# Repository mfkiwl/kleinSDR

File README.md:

# kleinSDR
Small SDR based on STM32.

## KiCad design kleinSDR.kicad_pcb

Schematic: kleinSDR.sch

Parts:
C1, C2, C3, C4, C5, C6, C7, C8, C9, C10, C11, C12, C13, C14, C15, C16, C17, C24, C25, C26, C28, C30, C33, C34, C35, C36, C37, C38, C39, C40, C41, C42, C43, C44, C46, C47, C48, C55, C58, C59, C61, C66, C72: 100nF; C_0603
C18, C19, C20, C21, C22, C23, C60, C62, C73, C74, C75, C76: 1nF; C_0603
C27, C29, C45: 4.7uF; C_0603
C31, C32: 2.2uF; C_0603
C49, C52, C63, C70: 10uF; C_0603
C50, C51: 470nF; C_0603
C53, C54, C67, C68, C69: 1uF; C_0603
C56, C57, C71: 220pF; C_0603
C64, C65: 220uF
J1: USB_B_Mini; USB_Mini-B_Lumberg_2486_01_Horizontal
J2: Frequency Dial; Pin_Header_Straight_1x04_Pitch2.54mm
J3: Boot0
J4: SWDP; Pin_Header_Straight_1x04_Pitch2.54mm
J5: UART
J6, J7: Line Out
J8: LINE IN
J9: MIC IN
J10: 30pin Board to Board
L1, L2: 47uH
Q1: BC857; SOT-23
R1, R2: 22E; R_0603
R3, R5: 10K; R_0603
R4, R11, R12, R22, R23, R32, R33: 47E; R_0603
R6, R7, R8, R9, R10, R15, R16, R17, R18, R21, R31: 100E; R_0603
R13, R14, R24, R25: 1K; R_0603
R19, R26, R27, R29, R30: 4k7; R_0603
R20: 680E; R_0603
R28: 47K; R_0603
SW1: PG6; SW_PUSH_6mm_h4.3mm
SW2: PB8; SW_PUSH_6mm_h4.3mm
SW3: PE4; SW_PUSH_6mm_h4.3mm
SW4: PG11; SW_PUSH_6mm_h4.3mm
SW5: PF0; SW_PUSH_6mm_h4.3mm
SW6: PB3; SW_PUSH_6mm_h4.3mm
SW7: PC1; SW_PUSH_6mm_h4.3mm
SW8: PA15; SW_PUSH_6mm_h4.3mm
SW9: PE2; SW_PUSH_6mm_h4.3mm
SW10: PG15; SW_PUSH_6mm_h4.3mm
SW11: PE3; SW_PUSH_6mm_h4.3mm
SW12: PE5; SW_PUSH_6mm_h4.3mm
SW13: PB0; SW_PUSH_6mm_h4.3mm
SW14: PB2; SW_PUSH_6mm_h4.3mm
SW15: PC4; SW_PUSH_6mm_h4.3mm
SW16: PC5; SW_PUSH_6mm_h4.3mm
SW17: PG2; SW_PUSH_6mm_h4.3mm
SW18: Volume; RotaryEncoder_Alps_EC12E_Vertical_H20mm
SW19: RF Gain; RotaryEncoder_Alps_EC12E_Vertical_H20mm
SW20: RIT; RotaryEncoder_Alps_EC12E_Vertical_H20mm
U1: FOX924B-16.000
U2: USBLC6-2SC6; SOT-23-6
U3: STM32F767ZITx; LQFP-144_20x20mm_Pitch0.5mm
U4, U6: WM8731; SSOP-28_5.3x10.2mm_Pitch0.65mm
U5: HY28B

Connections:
+3.3VA: C25.2, C27.2, R4.2, U3.33
+3.3VADC: C28.2, C29.2, R4.1, U3.32
+3V3: C30.2, C33.2, C34.2, C35.2, C36.2, C37.2, C38.2, C39.2, C40.2, C41.2, C42.2, C43.2, C44.2, C45.2, C47.2, C48.2, C49.2, C59.2, C61.2, C63.2, R5.2, R13.2, R14.2, R24.2, R25.2, U3.6, U3.17, U3.30, U3.39, U3.52, U3.62, U3.72, U3.84, U3.95, U3.108, U3.121, U3.131, U3.144, U4.1, U4.27, U6.1, U6.27
+5V: C24.2, J2.1
/ADC1: U3.42
/ADC2: U3.37
/ADC3: U3.13
/AUDIO_IN_I: C53.2, C56.2
/AUDIO_IN_Q: C54.2, C57.2
/AUDIO_OUT_I: C50.1
/AUDIO_OUT_Q: C51.1
/BAND0: U3.56
/BAND1: U3.100
/BAND2: U3.102
/ButtonBndM: C11.1, SW13.2, U3.46
/ButtonBndP: C12.1, SW14.2, U3.48
/ButtonF1: C8.1, SW8.2, U3.110
/ButtonF2: C9.1, SW9.2, U3.1
/ButtonF3: C10.1, SW10.2, U3.132
/ButtonF4: C14.1, SW11.2, U3.2
/ButtonF5: C15.1, SW12.2, U3.4
/ButtonG1: C1.1, SW1.2, U3.91
/ButtonG2: C2.1, SW2.2, U3.139
/ButtonG3: C6.1, SW3.2, U3.3
/ButtonG4: C7.1, SW4.2, U3.126
/ButtonM1: C3.1, SW5.2, U3.10
/ButtonM2: C4.1, SW6.2, U3.133
/ButtonM3: C5.1, SW7.2, U3.27
/ButtonPwr: C17.1, SW17.2, U3.87
/ButtonStpM: C13.1, SW15.2, U3.44
/ButtonStpP: C16.1, SW16.2, U3.45
/DAC1: U3.41
/EncFreq1: J2.2, U3.96
/EncFreq2: J2.3, U3.97
/EncRF1: C22.2, SW19.B, U3.81
/EncRF2: C19.2, SW19.A, U3.82
/EncRIT1: C23.2, SW20.B, U3.34
/EncRIT2: C20.2, SW20.A, U3.35
/EncVol1: C21.2, SW18.B, U3.134
/EncVol2: C18.2, SW18.A, U3.135
/I2C1_SCL: R32.2, U3.136
/I2C1_SDA: R33.2, U3.137
/I2C2_SCL: R22.1, R24.1, U3.69
/I2C2_SDA: R23.1, R25.1, U3.70
/I2C4_SCL: R11.1, R13.1, U3.54
/I2C4_SDA: R12.1, R14.1, U3.55
/LCD_BL: U3.116, U5.40
/LCD_CS: U3.123, U5.11
/LCD_D0: U3.85, U5.23
/LCD_D1: U3.86, U5.24
/LCD_D2: U3.114, U5.25
/LCD_D3: U3.115, U5.26
/LCD_D4: U3.58, U5.27
/LCD_D5: U3.59, U5.28
/LCD_D6: U3.60, U5.29
/LCD_D7: U3.63, U5.30
/LCD_D10: U3.64, U5.3
/LCD_D11: U3.65, U5.4
/LCD_D12: U3.66, U5.5
/LCD_D13: U3.67, U5.6
/LCD_D14: U3.68, U5.7
/LCD_D15: U3.77, U5.8
/LCD_D16: U3.78, U5.9
/LCD_D17: U3.79, U5.10
/LCD_RD: U3.118, U5.14
/LCD_RESET: U3.117, U5.15
/LCD_RS: U3.88, U5.12
/LCD_SDI: U5.17
/LCD_SDO: U5.16
/LCD_WR: U3.119, U5.13
/MICBIAS: R19.2, U3.93
/NRST: J4.1, U3.25
/PTT: C75.2, R31.2
/PTT_ON: U3.47
/PWR_DWN: U3.98
/SAI1_FS_B: R17.2, U3.21
/SAI1_MCLK_B: R21.1, U3.19
/SAI1_SCK_B: R15.2, U3.20
/SAI1_SD_A: R18.2, U3.122
/SAI1_SD_B: R16.2, U3.18
/SAI2_FS_B: R8.2, U3.26
/SAI2_MCLK_B: R10.1, U3.5
/SAI2_SCK_B: R6.2, U3.36
/SAI2_SD_A: R9.2, U3.80
/SAI2_SD_B: R7.2, U3.125
/SWCLK: J4.2, U3.109
/SWDIO: J4.3, U3.105
/TP_CS: U3.101, U5.32
/TP_IRQ: U3.89, U5.36
/TP_SCK: U3.74, U5.33
/TP_SDI: U3.29, U5.34
/TP_SDO: U3.28, U5.35
/UI_5V: U5.1
/USB_N: R1.1
/USB_OTG_FS_DM: R1.2, U3.103
/USB_OTG_FS_DP: R2.2, U3.104
/USB_P: R2.1
/xUSB_N: J1.2 (D-)
/xUSB_P: J1.3 (D+)
GND: C1.2, C2.2, C3.2, C4.2, C5.2, C6.2, C7.2, C8.2, C9.2, C10.2, C11.2, C12.2, C13.2, C14.2, C15.2, C16.2, C17.2, C18.1, C19.1, C20.1, C21.1, C22.1, C23.1, C24.1, C25.1, C26.1, C27.1, C28.1, C29.1, C30.1, C31.2, C32.2, C33.1, C34.1, C35.1, C36.1, C37.1, C38.1, C39.1, C40.1, C41.1, C42.1, C43.1, C44.1, C45.1, C46.1, C47.1, C48.1, C49.1, C52.1, C55.1, C56.1, C57.1, C58.1, C59.1, C60.1, C61.1, C62.1, C63.1, C66.1, C70.1, C71.1, C72.1, C73.1, C74.1, C75.1, C76.1, J1.5 (GND), J1.6 (Shield), J2.4, J4.4, R3.2, R26.2, R27.2, R28.1, SW1.1, SW2.1, SW3.1, SW4.1, SW5.1, SW6.1, SW7.1, SW8.1, SW9.1, SW10.1, SW11.1, SW12.1, SW13.1, SW14.1, SW15.1, SW16.1, SW17.1, SW18.C, SW19.C, SW20.C, U1.2, U3.16, U3.31, U3.38, U3.51, U3.61, U3.83, U3.94, U3.107, U3.120, U3.130, U4.11, U4.15, U4.21, U4.22, U4.28, U5.2, U5.19, U5.22, U5.39, U6.11, U6.15, U6.21, U6.22, U6.28
unnamed: C26.2, U1.4
unnamed: C31.1, U3.71
unnamed: C32.1, U3.106
unnamed: C50.2, U4.12
unnamed: C51.2, U4.13
unnamed: C52.2, C55.2, U4.16
unnamed: C53.1, U4.20
unnamed: C54.1, U4.19
unnamed: C66.2, R19.1
unnamed: C67.1, U6.20
unnamed: C67.2, R26.1, R29.1
unnamed: C68.1, U6.19
unnamed: C68.2, R27.1, R30.1
unnamed: C69.1, U6.18
unnamed: C69.2, C71.2, C73.2, R20.1, R28.2
unnamed: C70.2, C72.2, U6.16
unnamed: C74.2, R29.2
unnamed: C76.2, R30.2
unnamed: R3.1, U3.138
unnamed: R5.1, U3.143
unnamed: R6.1, U4.3
unnamed: R7.1, U4.4
unnamed: R8.1, U4.5, U4.7
unnamed: R9.1, U4.6
unnamed: R10.2, U4.25
unnamed: R11.2, U4.24
unnamed: R12.2, U4.23
unnamed: R15.1, U6.3
unnamed: R16.1, U6.4
unnamed: R17.1, U6.5, U6.7
unnamed: R18.1, U6.6
unnamed: R21.2, U6.25
unnamed: R22.2, U6.24
unnamed: R23.2, U6.23
unnamed: U1.3, U3.23
VBUS: J1.1 (VBUS)
VDDA: C46.2, C58.2, U4.8, U4.14, U6.8, U6.14

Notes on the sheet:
USB Connector
Buttons
Rotary Encoders
Frequency Dial Optical Encoder
SWDP & Debug Connectors
Vdd, Vbat Decoupling
Ceramic Low ESR
Vdda, Vref Decoupling
TO DO: 1. Check all pin assignments 2. Check HSE/clock design 3. Design power circuit 4. Can I make Cap 1 & 2 4.7uF? 5. Do paddle dah and dit connections
HY28B Connector
I/Q RX/TX Audio CODEC
Analog RX/TX Audio CODEC

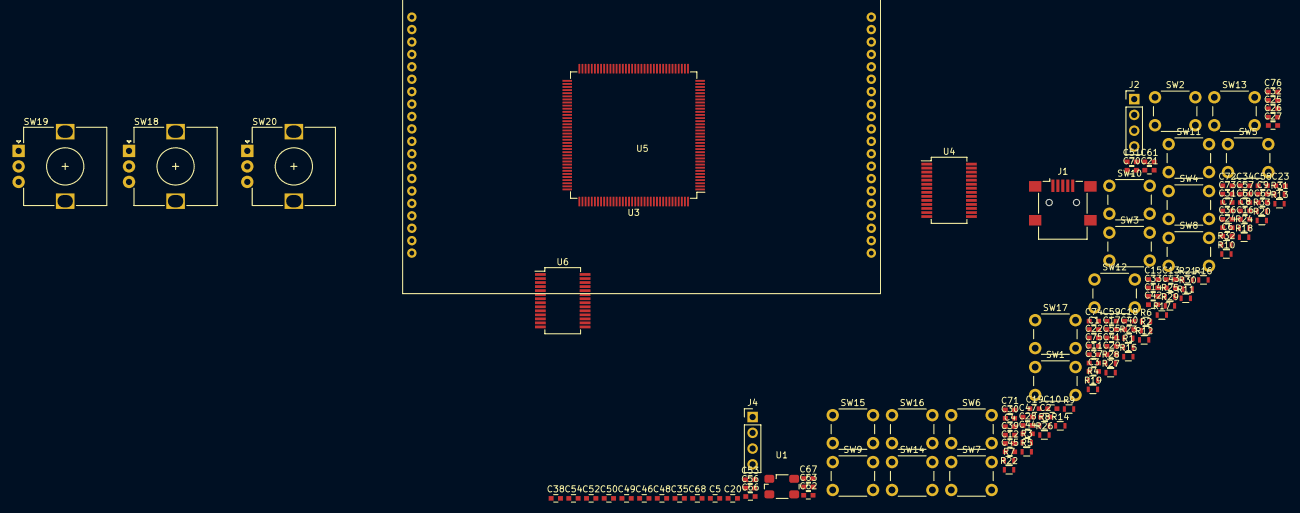
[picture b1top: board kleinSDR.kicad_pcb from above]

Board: 2 copper layers, 135 parts (0 on the bottom side), 118 nets, no tracks yet.

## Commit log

2018-08-22 Add power, boot, NRST and USB to schematic
2018-08-28 Changed MCU to STM32F407VGT6
2018-08-30 Add buttons, encoders, USB and power
    Add buttons, encoders, USB and power
2018-08-31 Decided to go back to F7
2018-08-31 Add buttons, encoders, DFU USB connector, decoupling caps
2018-08-31 Add HY28B connection
2018-08-31 Change front face immage
2018-09-01 TX/RX Audio CODEC
2018-09-01 Add analog audio codec circuit
2018-09-01 Connect 30pin board to board
2018-09-02 Further updates
2018-09-03 Completed initial layout
2018-09-05 Review/checked pin assignments, clock design, power circuits

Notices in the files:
kleinSDR.sch:
CERN OHL v1.2
